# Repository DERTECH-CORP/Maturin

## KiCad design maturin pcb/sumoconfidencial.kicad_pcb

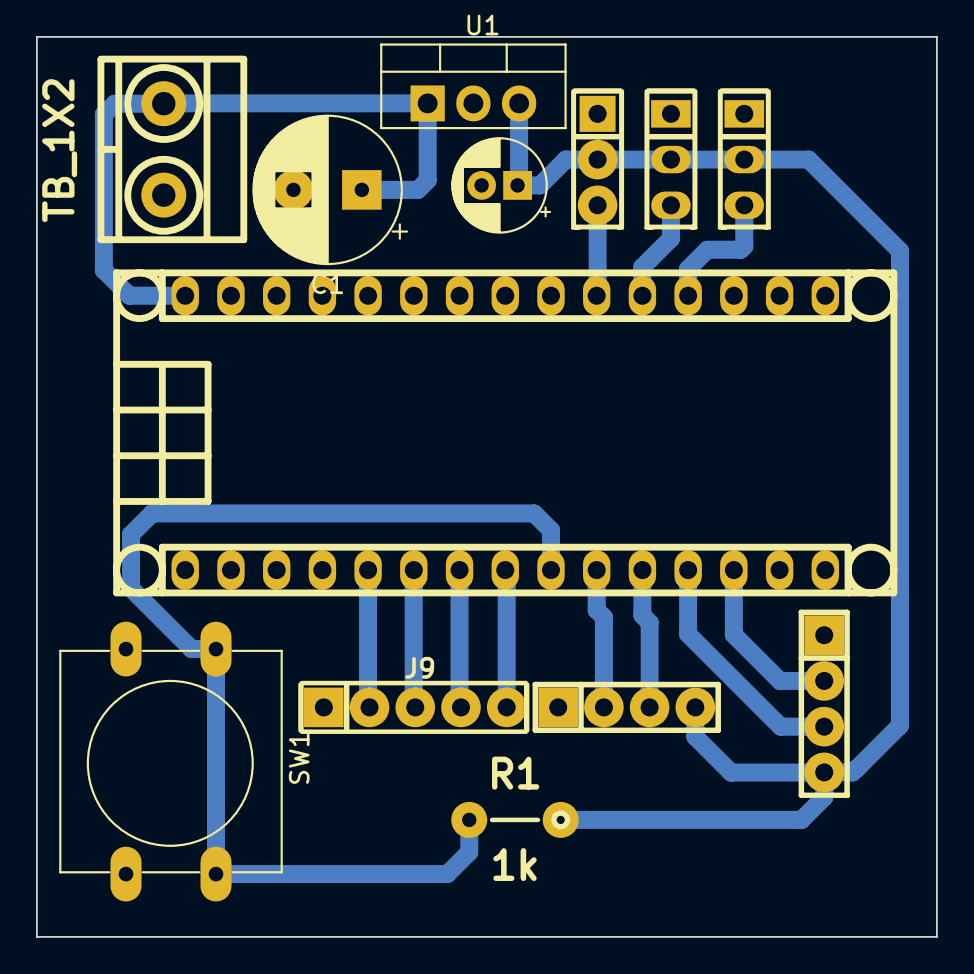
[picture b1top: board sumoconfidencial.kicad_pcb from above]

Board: 2 copper layers, 50.0 x 50.0 mm, 13 parts (0 on the bottom side), 15 nets.

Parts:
C1: 470μF; CP_Radial_D8.0mm_P3.80mm
C2: 1μF; CP_Radial_D5.0mm_P2.00mm
J2: CNY70 1; Pin_Header_3
J3, J8: conector sensor ultrasonido; pin_strip_4
J4: TB_1X2; BORNERA2_AZUL
J5: Arduino_Nano_Header; arduino_nano_header
J6: CNY70 2; Pin_Header_3
J7: CNY70 3; Pin_Header_3
J9: HEADER_5; Pin_Header_5
R1: 1k; RES0.2
SW1: SW_Push; SW_PUSH-12mm
U1: LM78M05_TO220; TO-220-3_Vertical

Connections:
+5V: C2.1, J2.2, J3.4, J6.2, J7.2, J8.4, R1.1, U1.3 (VO)
+BATT: C1.1, J4.1, J5.30 (VIN), U1.1 (VI)
/swichin: J5.9 (D6/AIN0), R1.2, SW1.1
ECNO 1: J5.10 (D7/AIN1), J8.2
ECNO 2: J3.2, J5.13 (D10/SS)
GND: C1.2, C2.2, J2.1, J3.1, J4.2, J5.29 (GND), J6.1, J7.1, J8.1, J9.1, SW1.2, U1.2 (GND)
IN1: J5.5 (D2/INT0), J9.2
IN2: J5.6 (D3/INT1), J9.3
IN3: J5.7 (D4/T0), J9.4
IN4: J5.8 (D5/T1), J9.5
OUT 1: J2.3, J5.19 (A0)
OUT 2: J5.20 (A1), J6.3
OUT 3: J5.21 (A2), J7.3
TRIG 1: J5.11 (D8/ICP), J8.3
TRIG 2: J3.3, J5.12 (D9/0C1)

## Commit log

2023-08-06 Cree el PCB
2023-08-06 elimine el pcb
2023-08-06 pcb_maturin_1
    pcb
2023-08-06 Creacion de la rama diseño 3D
2023-08-06 me pelo la verga y creo la carpeta de 3d
2023-08-06 Subo el codigo
2023-08-08 Subo el codigo version 2
2023-08-08 Subo la PCB de maturin version 2
